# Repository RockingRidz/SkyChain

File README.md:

# SkyChain

SkyChain is a compact, wearable smart keychain designed to clip onto your belt, fit in your pocket, or go anywhere with you. Whenever you spot a plane flying overhead or want to check real-time flight telemetry, SkyChain delivers live aircraft tracking data directly to your OLED screen.

## Bill of Materials (BOM)

| Part | Description | Qty | Price |
| :--- | :--- | :---: | :--- |
| ESP32-C3-DevKitM-1 | Microcontroller (U3) | 1 | \$10.00 |
| TP4056-42-ESOP8 | Battery Charger IC (U1) | 1 | \$2.00 |
| AMS1117-3.3 | LDO Voltage Regulator (U2) | 1 | \$1.50 |
| USB_C_Receptacle_USB2.0_16P | USB Interface (J1) | 1 | \$2.00 |
| Conn_01x04_Socket | Display Connector (J3) | 1 | \$1.00 |
| Conn_01x02_Socket | Battery Connector (J2) | 1 | \$1.00 |
| SW_Push | Buttons (SW1-SW3) | 3 | \$0.50 |
| Piezo Buzzer | Audio Buzzer (BZ1) | 1 | \$1.50 |
| NPN Transistor | S8050 Transistor (Q1) | 1 | \$1.00 |
| SMD Resistors | Resistors (R1-R7) | 1 | \$4.00 |
| SMD Capacitors | Capacitors (C1-C4) | 1 | \$3.00 |
| 3D Printed / Acrylic | Enclosure & Window | 1 | \$1.50 |
| **Total** | | | **\$30.00** |

---

## Overview & How It Works

SkyChain fetches live overhead tracking data via the **OpenSky Network API** to give you real-time details about aircraft above you:

- **Flight Callsign & Identification**
- **Country of Origin**
- **Altitude & Flight Height**

Every time SkyChain queries the OpenSky API or receives updated telemetry, it updates its onboard display to show current flight tracking data.

---

## Core Features

- **Real-Time Flight Tracking**: Connects via Wi-Fi to the OpenSky REST API for live aircraft callsigns, countries, and altitude metrics.
- **Interactive Multi-Function UI**: Controlled via a 2-button tactile layout supporting single clicks, double-clicks, and long-presses to navigate menus.
- **Visual Display**: Integrated high-contrast 128x64 SSD1306 OLED screen for displaying clear flight stats and system menus.
- **Autonomous Battery Management**: Onboard USB-C charging and LiPo battery regulation for untethered daily wear.
- **Compact Keychain Form Factor**: Portable, lightweight hardware layout designed for everyday carry with an integrated spline window and acrylic viewing pane.

---

## Custom Hardware Design

Designing and routing the printed circuit board and 3D-printed enclosure has been an exciting hardware challenge:

- **Microcontroller Core**: ESP32 module managing Wi-Fi requests, display driving, and button debounce logic.
- **Power System**: Lithium battery charging paired with a low-dropout regulator and USB-C power delivery.
- **Enclosure Geometry**: Custom CAD model featuring a 2.0 mm wall enclosure, reinforced keychain mount, and a recessed internal ledge for a flush-fit acrylic window.
- **Optimized Passives**: SMD passive array for power decoupling, USB pull-downs, and robust circuit stability.
- THIS WAS MY 3RD PCB DESIGN AND PROLLY THE MOST COMPLEX IVE MADE!!
-

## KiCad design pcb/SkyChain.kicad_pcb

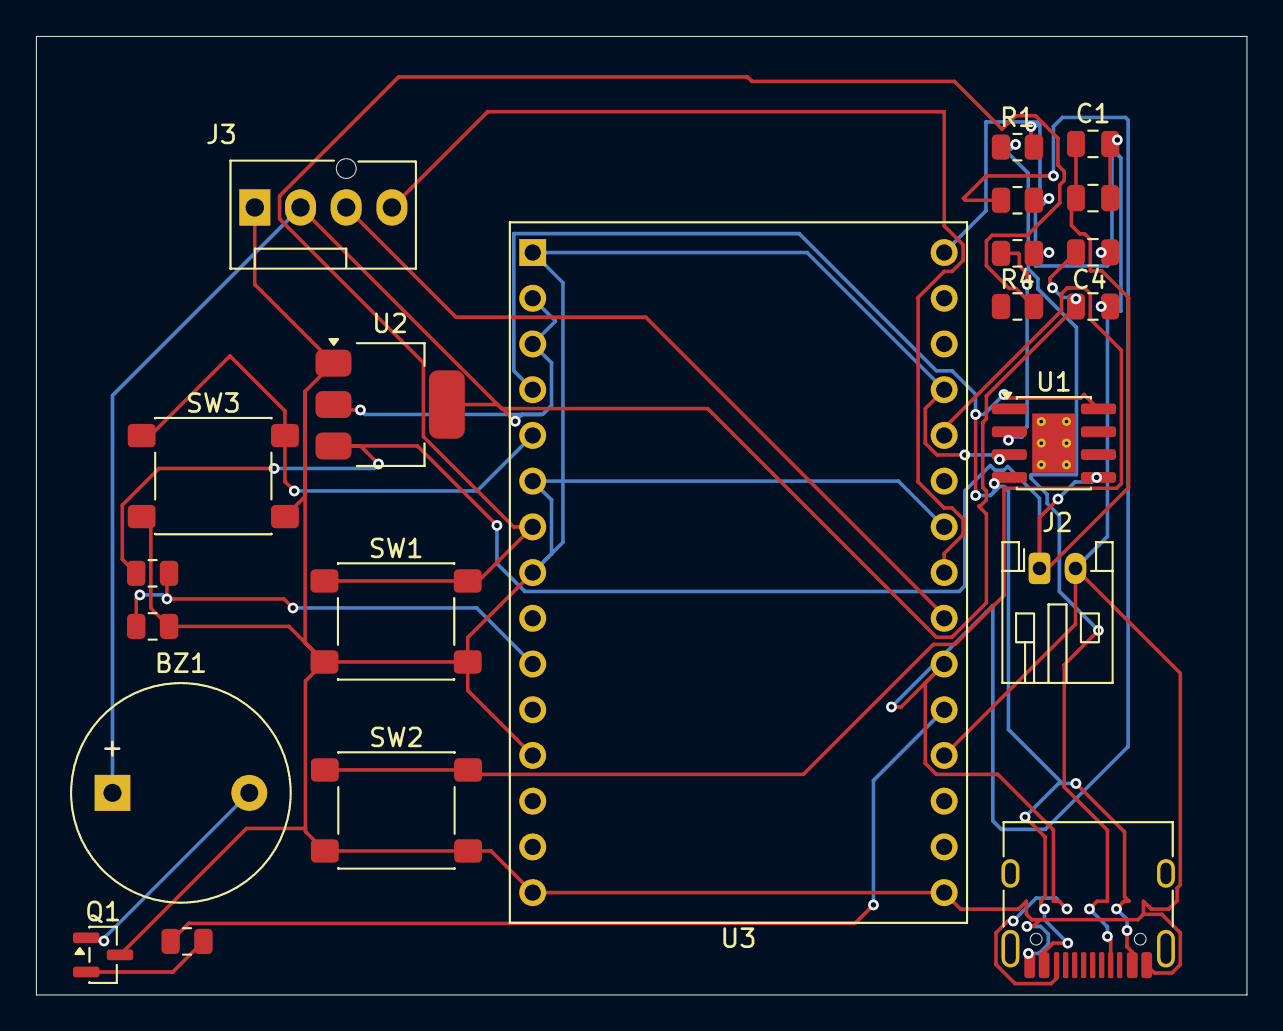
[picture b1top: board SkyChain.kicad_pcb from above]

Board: 2 copper layers, 67.2 x 53.2 mm, 22 parts (0 on the bottom side), 16 nets.

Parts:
BZ1: Buzzer; Buzzer_12x9.5RM7.6
C1, C3: 10uF; C_0805_2012Metric
C2, C4: 100nF; C_0805_2012Metric
J1: USB_C_Receptacle_USB2.0_16P; USB_C_Receptacle_HRO_TYPE-C-31-M-12
J2: Conn_01x02_Socket; JST_PH_S2B-PH-K_1x02_P2.00mm_Horizontal
J3: Conn_01x04_Socket; FanPinHeader_1x04_P2.54mm_Vertical
Q1: NPN; SOT-23
R1, R2: 5.1k; R_0805_2012Metric
R3: 1.2k; R_0805_2012Metric
R4, R5: 1k; R_0805_2012Metric
R6, R7: 100k; R_0805_2012Metric
SW1, SW2, SW3: SW_Push; SW_SPST_PTS645Sx43SMTR92
U1: TP4056-42-ESOP8; SOIC-8-1EP_3.9x4.9mm_P1.27mm_EP2.41x3.3mm_ThermalVias
U2: AMS1117-3.3; SOT-223-3_TabPin2
U3: ESP32-C3-DevKitM-1

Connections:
GND: C1.2, C2.2, C3.2, C4.2, J1.A1 (GND), J1.A12 (GND), J1.B1 (GND), J1.B12 (GND), J2.2, J3.1, Q1.3 (E), R1.2, R2.2, R3.2, R7.2, SW1.2, SW2.2, SW3.2, U1.3 (GND), U2.1 (GND), U3.1 (GND), U3.6 (GND), U3.8 (GND), U3.12 (GND), U3.15 (GND), U3.16 (GND), U3.19 (GND), U3.24 (GND), U3.27 (GND), U3.30 (GND)
unnamed: BZ1.1 (+), C3.1, C4.1, J3.2, U2.2 (VO), U3.2 (3V3), U3.3 (3V3)
unnamed: BZ1.2 (-), Q1.1 (C)
unnamed: J1.A5 (CC1), R1.1
unnamed: J1.B5 (CC2), R2.1, U3.21 (IO5)
unnamed: C1.1, C2.1, J2.1, R6.1, U1.5 (BAT), U2.3 (VI)
unnamed: J3.3, U3.22 (IO6)
unnamed: J3.4, U3.23 (IO7)
unnamed: Q1.2 (B), R5.2
unnamed: J1.A4 (VBUS), J1.A9 (VBUS), J1.B4 (VBUS), J1.B9 (VBUS), U1.4 (V_{CC}), U1.8 (CE), U3.4 (IO2)
unnamed: R3.1, U1.2 (PROG)
unnamed: R6.2, R7.1, U3.10 (IO1)
unnamed: SW3.1, U3.5 (IO3)
unnamed: R5.1, U3.20 (IO4)
unnamed: SW2.1, U3.26 (IO9)
unnamed: R4.2, SW1.1, U3.7 (RST)

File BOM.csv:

# SkyChain – bill of materials

<!-- Generated by Half Life from project cmuv3c9td0d4301smn5wbxmmh. Edits here are overwritten on the next sync. -->
<!-- Generated: 1970-01-01T00:00:00.000Z -->

> [!NOTE]
> This parts list is mirrored from [Half Life](https://halflife.hackclub.com). Editing it here will not change the platform's copy, and the next sync overwrites this file.

| Week | Tier | Parts funding |
| --- | --- | --- |
| Week 1 | Tier 1 | $30.00 |

| Component / Item | Description / Model | Qty | Estimated Cost |
| :--- | :--- | :--- | :--- |
| **Microcontroller (U3)** | ESP32-C3-DevKitM-1 | 1 | $6.00 |
| **Battery Charger (U1)** | TP4056-42-ESOP8 LiPo Charger IC | 1 | $2.00 |
| **Voltage Regulator (U2)** | AMS1117-3.3 LDO Voltage Regulator | 1 | $1.50 |
| **USB Interface (J1)** | USB_C_Receptacle_USB2.0_16P | 1 | $2.00 |
| **Display / Peripheral Connector (J3)** | Conn_01x04_Socket | 1 | $1.00 |
| **Battery Connector (J2)** | Conn_01x02_Socket | 1 | $1.00 |
| **Tactile Switches (SW1, SW2, SW3)** | SW_Push Momentary Tactile Buttons | 3 | $1.50 |
| **Buzzer (BZ1)** | Piezo Buzzer | 1 | $1.50 |
| **Transistor (Q1)** | NPN Transistor (e.g., S8050) | 1 | $1.00 |
| **Resistors (R1, R2)** | 5.1kΩ SMD Resistors | 2 | $1.00 |
| **Resistors (R3, R5)** | 1.2kΩ & 1kΩ SMD Resistors | 2 | $1.00 |
| **Resistors (R4, R6, R7)** | 1kΩ & 100kΩ SMD Resistors | 3 | $1.50 |
| **Capacitors (C1, C3)** | 10µF SMD Capacitors | 2 | $1.00 |
| **Capacitors (C2, C4)** | 100nF SMD Capacitors | 2 | $1.00 |
| **Enclosure & Acrylic** | 3D Printed Enclosure & Acrylic Window Pane | 1 set | $3.00 |
| **Total Estimated Cost** | | | **$25.00** |
